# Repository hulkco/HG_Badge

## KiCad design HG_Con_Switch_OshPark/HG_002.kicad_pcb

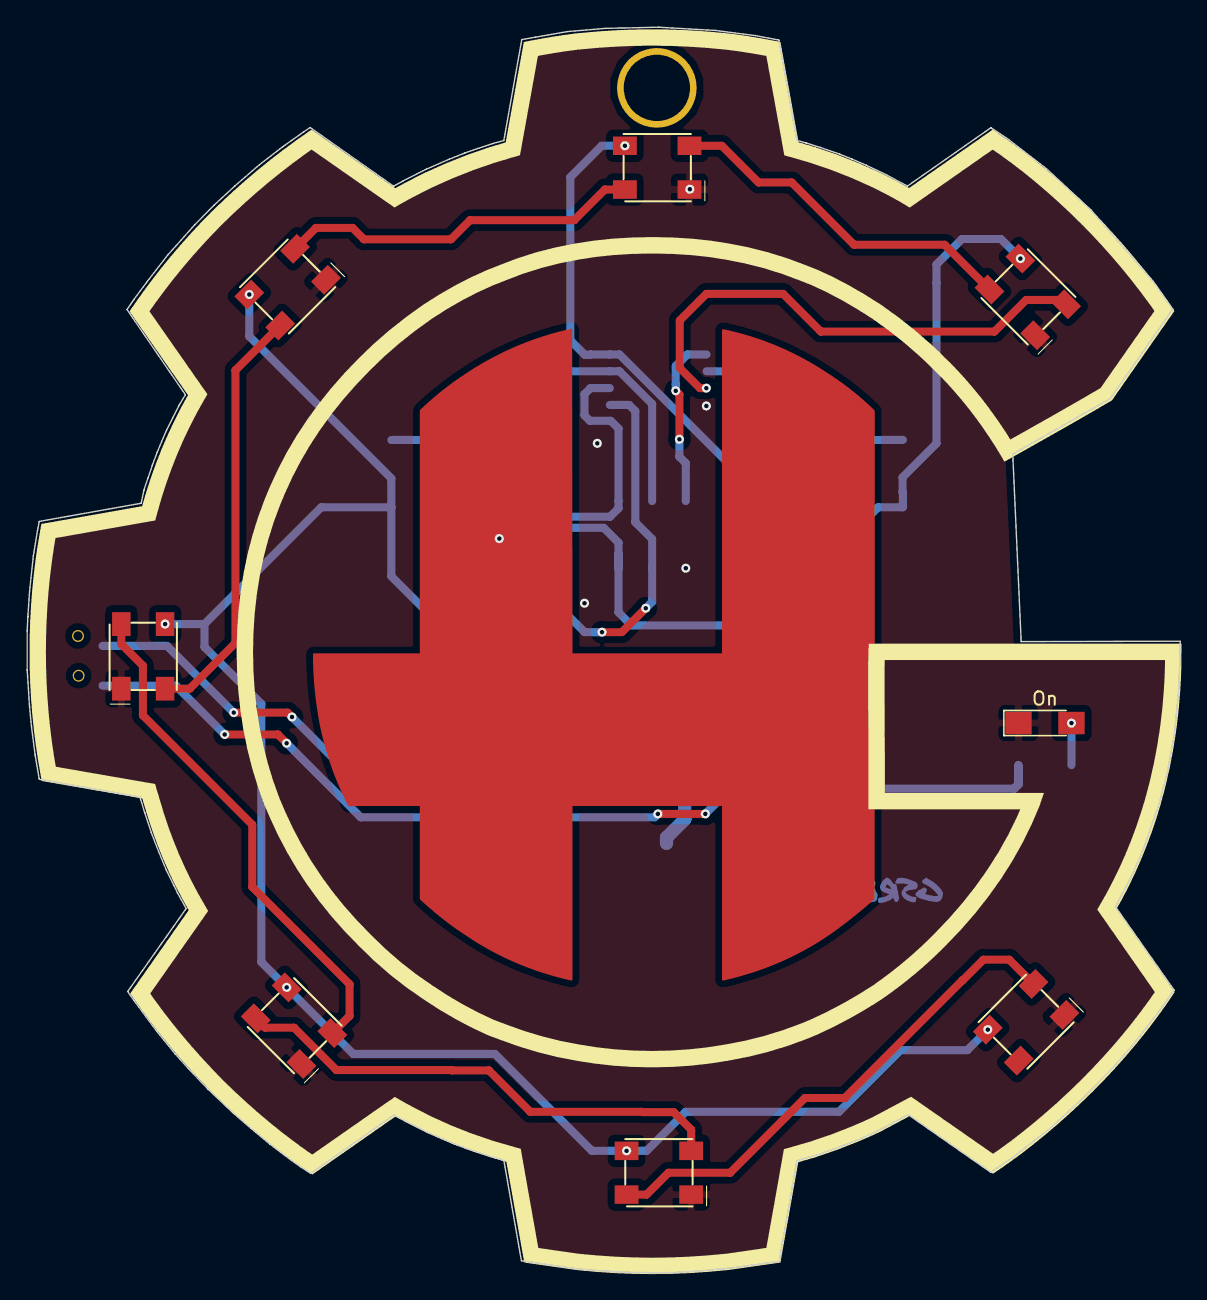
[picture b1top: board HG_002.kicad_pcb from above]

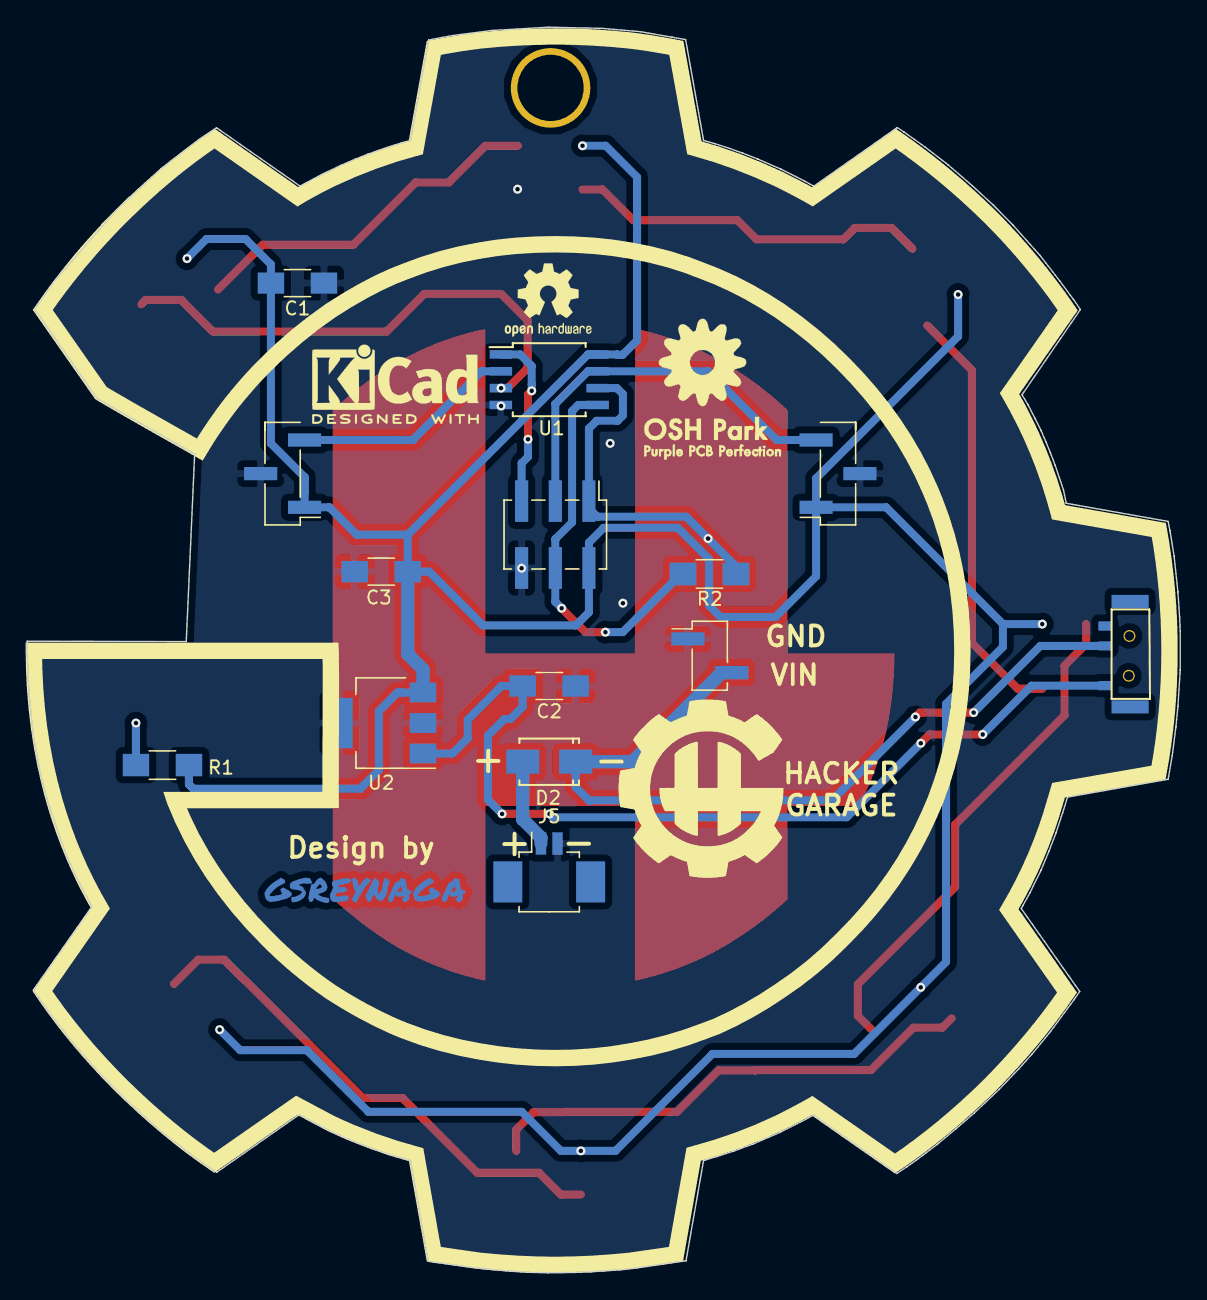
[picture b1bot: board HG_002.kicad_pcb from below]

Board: 2 copper layers, 87.0 x 94.0 mm, 28 parts (17 on the bottom side), 18 nets.

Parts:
C1: 22nF; C_1206_HandSoldering
C2, C3: 4.7uF; C_1206_HandSoldering
CAP1: HG_CAPSENSE_H; H_CapSense
D2: MBRA140; DIODE-SMA
J1: CONN_01X03; Pin_Header_Straight_1x03_Pitch2.54mm_SMD_Pin1Left
J2: CONN_01X03; Pin_Header_Straight_1x03_Pitch2.54mm_SMD_Pin1Right
J3: CONN_02X03; Pin_Header_Straight_2x03_Pitch2.54mm_SMD
J4: CONN_01X02; Pin_Header_Straight_1x02_Pitch2.54mm_SMD_Pin1Left
J5: CONN_01X02; Molex_PicoBlade_53261-0271_02x1.25mm_Angled
LED1, LED2, LED3, LED4, LED5, LED6, LED7: WS2812B
MountinHoleBagde: MountingHole_5mm_Badge; MountingHole_3.5mm_Pad
On: ON; LED_1206_HandSoldering
R1: 1k; R_1206_HandSoldering
R2: 1M Ohms; R_1206_HandSoldering
S2: MSK12C02_SWITCH-SLIDE-SPDT; MSK12C02
U1: ATTINY85-20SU; SOIJ-8_5.3x5.3mm_Pitch1.27mm
U2: LM340MP-5.0/NOPB; SOT-223-3Lead_TabPin2
svg2mod: G***; FirmaCuMask
svg2mod#2: G***; HG_SmallLogo
svg2mod#3: G***; HG_SilkS.Back.2
svg2mod#4: G***; HG_Edge.SilkS.3

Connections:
3-A3: J1.3, U1.2
4-A2: LED1.2, U1.3
+5V: C1.1, C3.1, J1.1, J2.1, J3.2, LED1.3, LED2.3, LED3.3, LED4.3, LED5.3, LED6.3, LED7.3, R1.1, U1.8, U2.3
GND: C1.2, C2.2, C3.2, J1.2, J2.2, J3.6, J4.1, J5.2, LED1.1, LED2.1, LED3.1, LED4.1, LED5.1, LED6.1, LED7.1, On.1, U1.4, U2.2
MISO-1-PWM: J3.1, R2.2, U1.6
MOSI-0-PWM: J3.4, R2.1, U1.5
unnamed: C2.1, S2.1, U2.1
unnamed: On.2, R1.2
unnamed: LED1.4, LED2.2
unnamed: LED2.4, LED3.2
unnamed: LED3.4, LED4.2
unnamed: LED4.4, LED5.2
unnamed: LED5.4, LED6.2
unnamed: LED6.4, LED7.2
RESET: J3.5, U1.1
SCK-2-A1: J2.3, J3.3, U1.7
VBAT: D2.2, J5.1
VCC: D2.1, J4.2, S2.2

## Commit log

2018-11-08 Firts upload
    Hacker Garage Badge
2018-11-15 Update 15 Nov 2018
2018-12-05 Update Back Silk
